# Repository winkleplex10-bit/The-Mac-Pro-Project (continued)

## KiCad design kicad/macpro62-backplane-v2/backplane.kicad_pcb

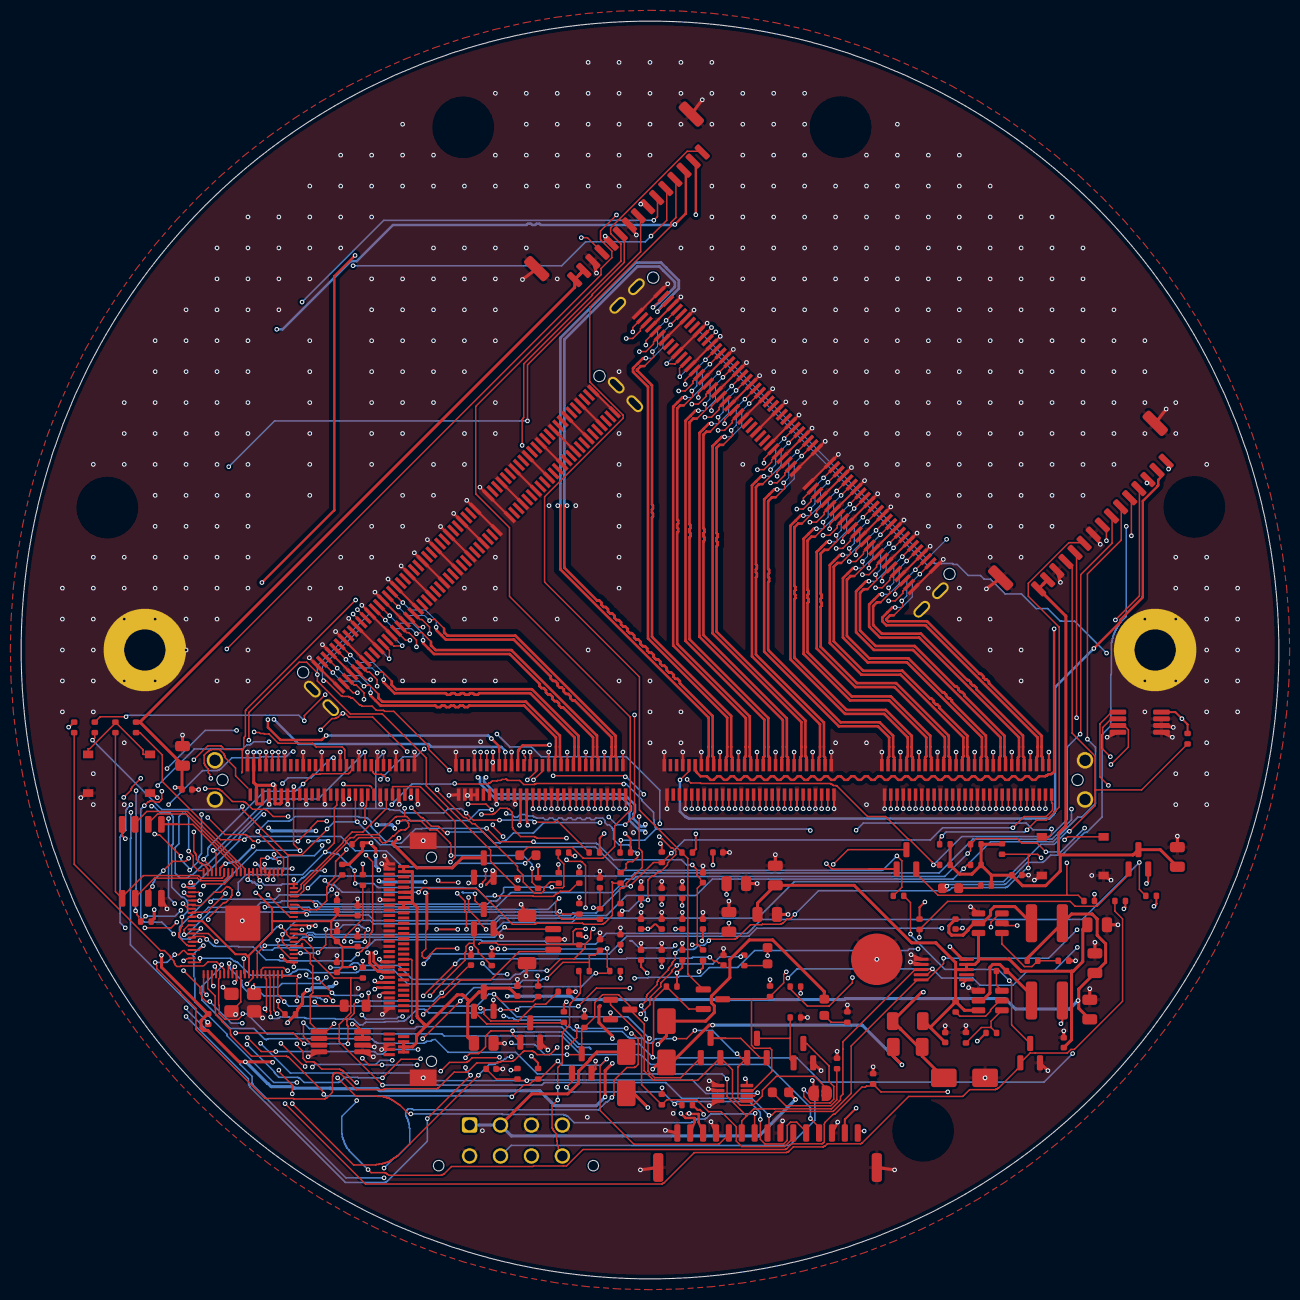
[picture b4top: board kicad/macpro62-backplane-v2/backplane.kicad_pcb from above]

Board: 4 copper layers, 122.0 x 122.0 mm, 152 parts (0 on the bottom side), 202 nets.

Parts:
C1, C5, C8, C9, C12, C14, C16, C18, C19, C21, C22, C23, C24, C25, C26, C27, C28, C32, C33, C34, C35, C38, C39: 100nF 16V X7R 0402; C_0402_1005Metric
C2, C3, C4, C6, C7, C10, C11, C13, C15, C17: 22uF 25V X5R 0805; C_0805_2012Metric
C20: 1uF 25V X5R 0402; C_0402_1005Metric
C29, C30, C31: 4.7uF 10V X5R 0402; C_0402_1005Metric
C36, C37: 15pF 50V C0G 0402; C_0402_1005Metric
D1, D2: SS34 3A 40V Schottky SMA; D_SMA
D3: SMAJ15A TVS SMA; D_SMA
D4, D5: BAT54A (LBAT54ALT1G); SOT-23
D6, D7, D8, D9, D10: LED red 0603; LED_0603_1608Metric
F1: 3A 1206 fast fuse (0466003.NRHF class); Fuse_1206_3216Metric
H1, H2: MountingHole D4 plated (GND); MountingHole_4mm_Pad
H3: M.2 2242 standoff pad (DNP option); MP62_M2_Standoff_SMT_M2_Pad5.0
J1: ME1022410103011 Mini Cool Edge 224 (C4941560, 0 s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; MP62_CPULINK_MiniCoolEdge_224P_Vertical_SMT_PLACEHOLDER
J2: Molex 43045-0812 Micro-Fit 2x4 (C277661); Molex_Micro-Fit_3.0_43045-0812_2x04_P3.00mm_Vertical
J3: BM15B-GHS-TBT (C5305069) Face P AUX; JST_GH_BM15B-GHS-TBT_1x15-1MP_P1.25mm_Vertical
J4: BM15B-GHS-TBT (C5305069) Face S AUX; JST_GH_BM15B-GHS-TBT_1x15-1MP_P1.25mm_Vertical
J6: BM15B-GHS-TBT (C5305069) IOB-LINK; JST_GH_BM15B-GHS-TBT_1x15-1MP_P1.25mm_Vertical
J7: M.2 M-key socket LOTES APCI0107 class (C841661) -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; MP62_M2_MKey_SMT_H4.2_PLACEHOLDER
J8: BM03B-SRSS-TB SWD (DNP); JST_SH_BM03B-SRSS-TB_1x03-1MP_P1.00mm_Vertical
J9: MCIO 124P RA G97R24332HR class (C4867471, 0 stock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; MP62_MCIO_124P_RA_SFF-TA-1016
J10: MCIO 124P RA (C4867471) -> Face S x4; MP62_MCIO_124P_RA_SFF-TA-1016
JP1: BENCH: bridges the Hall interlock (open = normal); SolderJumper-2_P1.3mm_Open_RoundedPad1.0x1.5mm
L1, L2: 4.7uH 2A 4x4 (SWPA4030S4R7MT); L_Changjiang_FNR4030S
L3: 3.3uH 0806 (FNR201610S3R3MT, RP2350 VREG); L_0805_2012Metric
Q1, Q2, Q3, Q5, Q6, Q7, Q8: AO3401A P-MOS; SOT-23
Q4, Q9, Q10, Q11: 2N7002 N-MOS; SOT-23
R1: 33k 1% 0402; R_0402_1005Metric
R2, R4, R7, R8, R9, R10, R13, R14, R15, R16, R17, R18, R19, R20, R21, R23, R24, R25, R26, R29, R30, R33, R34, R35, R36, R39, R40, R42, R43, R44, R45, R46, R47, R48, R49: 10k 1% 0402; R_0402_1005Metric
R3: 56k 1% 0402; R_0402_1005Metric
R5: 100k 1% 0402 (U6 EN, always on); R_0402_1005Metric
R6: 100k 1% 0402 (U7 off until the MCU enables 5V_SBY); R_0402_1005Metric
R11, R12, R55: 100k 1% 0402; R_0402_1005Metric
R22, R31, R32, R41, R54, R58, R60, R61: 1k 1% 0402; R_0402_1005Metric
R27, R28, R37, R38, R50, R51, R52, R53: 2.2k 1% 0402; R_0402_1005Metric
R56: 10k 1% 0402 (12V LED); R_0402_1005Metric
R57: 10k 1% 0402 (11V_SB LED); R_0402_1005Metric
R59, R62, R63: 33R 1% 0402; R_0402_1005Metric
R100: 10mR 1% 1W 1206 shunt; R_1206_3216Metric
SW1: BOOTSEL (TS-1187A); SW_Push_1P1T_XKB_TS-1187A
SW2: BENCH power button (TS-1187A); SW_Push_1P1T_XKB_TS-1187A
U1: RP2350B QFN-80 (C42415655); QFN-80-1EP_10x10mm_P0.4mm_EP3.4x3.4mm
U2: W25Q128JVSIQ (C97521, basic); SOIC-8_5.3x5.3mm_P1.27mm
U3: TMP1075DGKR @0x48 core side (C2864807); VSSOP-8_3x3mm_P0.65mm
U4: TMP1075DGKR @0x49 PSU side (C2864807); VSSOP-8_3x3mm_P0.65mm
U5: INA226AIDGSR @0x40 (C49851); VSSOP-10_3x3mm_P0.5mm
U6: TPS563201DDCR (C116592) -> 3V3_SB; SOT-23-6
U7: TPS563201DDCR (C116592) -> 5V_SBY; SOT-23-6
U8: SN74LVC1G74DCUR thermal latch (C70285); VSSOP-8_2.3x2mm_P0.5mm
Y1: 12MHz 3225 crystal 20pF; Crystal_SMD_3225-4Pin_3.2x2.5mm

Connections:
3V3_AUX_P: C13.1, C14.1, J3.1, J3.2, Q1.3, R26.2, R27.2, R28.2, R29.2, R30.2, R31.2
3V3_AUX_S: C15.1, C16.1, J4.1, J4.2, Q2.3, R36.2, R37.2, R38.2, R39.2, R40.2, R41.2
3V3_M2: C17.1, C18.1, J7.2, J7.4, J7.12, J7.14, J7.16, J7.18, J7.70, J7.72, J7.74, Q3.3
3V3_SB: C1.1, C6.1, C7.1, C19.1, C21.1, C22.1, C23.1, C24.1, C25.1, C26.1, C27.1, C28.1, C29.1, C38.1, D10.2, J1.B107, J1.B108, J6.1, J6.2, JP1.1, L1.2, Q1.2, Q2.2, Q3.2, Q5.2, Q6.2, R1.1, R7.2, R8.2, R9.2, R13.2, R14.2, R15.2, R16.2, R17.2, R18.2, R19.2, R20.2, R21.2, R23.2, R24.2, R25.2, R33.2, R34.2, R35.2, R42.2, R43.2, R44.2, R45.2, R46.2, R47.2, R48.2, R49.2, R50.2, R51.2, R52.2, R53.2, R59.1, U1.5, U1.15, U1.24, U1.29, U1.41, U1.50, U1.59, U1.60, U1.64, U1.68, U1.69, U1.76, U2.8, U3.8, U4.7, U4.8, U5.6, U8.8
5V_SBY: C10.1, C11.1, J1.A107, J1.A108, J1.A110, J1.A111, J1.B110, J1.B111, L2.2, R3.1
11V_SB_IN: D2.2, D9.2, J2.7
12V_MAIN_IN: D1.2, D8.2, J2.1, J2.2
AUXP_EN_N: Q1.1, R7.1, U1.37
AUXS_EN_N: Q2.1, R8.1, U1.19
BOOTSEL_N: R61.2, SW1.1
BP_OTEMP_N: D5.2, R21.1, U3.3, U4.3
BST_3V3_SB: C5.1, U6.6
BST_5V_SBY: C9.1, U7.6
CB_CARRIER_HOT_N: J1.A98, R44.1, U1.13
CB_FAN_PWM: J1.B96, U1.6
CB_FAN_TACH: J1.B98, U1.2
CB_I2C0_SCL: J1.B90, R50.1, U1.80
CB_I2C0_SDA: J1.B92, R51.1, U1.79
CB_PLTRST_N: J1.A95, R22.1, R32.1, U1.54
CB_PWRBTN_N: J1.A86, R42.1, U1.57
CB_PWR_ALERT_N: J1.A105, R43.1, U1.12
CB_RSMRST_N: J1.A92, U1.16
CB_SUS_S3_N: J1.A89, Q4.1, U1.21
CB_SUS_S45_N: J1.A90, U1.58
CB_THERMTRIP_N: D4.1, J1.A96, R18.1
CB_UART0_RX: J1.B95, U1.78
CB_UART0_TX: J1.B93, U1.77
CB_VIN_PWR_OK: J1.A93, U1.14
CC_PRSNT1_N: J1.A1, R45.1, U1.53
CC_PRSNT2_N: J1.A112, R46.1, U1.11
DVDD: C30.1, C31.1, C32.1, C33.1, C34.1, L3.2, U1.10, U1.32, U1.51, U1.65
EN_3V3: R5.1, U6.5
EN_5V: R6.1, U1.40, U7.5
FB_3V3_SB: R1.2, R2.1, U6.4
FB_5V_SBY: R3.2, R4.1, U7.4
FP_HOLD: Q10.1, R23.1, U1.36
FP_LEDA: D6.2, R31.1
FP_MCIO_PRSNT_N: J9.B12, R24.1, U1.47
FP_MOD_LED_N: D6.1, J3.15
FP_PERST_N: J9.B11, Q10.3, R22.2
FP_PRSNT_N: J3.4, R25.1, U1.42
FP_PWR_EN: J3.5, U1.49
FP_PWR_GOOD: J3.6, R26.1, U1.43
FP_REFCLK_N: J1.A52, J9.A12
FP_REFCLK_P: J1.A51, J9.A11
FP_RX0_N: J1.B49, J9.A3
FP_RX0_P: J1.B48, J9.A2
FP_RX1_N: J1.B46, J9.A6
FP_RX1_P: J1.B45, J9.A5
FP_RX2_N: J1.B43, J9.A15
FP_RX2_P: J1.B42, J9.A14
FP_RX3_N: J1.B40, J9.A18
FP_RX3_P: J1.B39, J9.A17
FP_RX4_N: J1.B37, J9.A21
FP_RX4_P: J1.B36, J9.A20
FP_RX5_N: J1.B34, J9.A24
FP_RX5_P: J1.B33, J9.A23
FP_RX6_N: J1.B31, J9.A33
FP_RX6_P: J1.B30, J9.A32
FP_RX7_N: J1.B27, J9.A36
FP_RX7_P: J1.B26, J9.A35
FP_RX8_N: J1.B24, J9.A40
FP_RX8_P: J1.B23, J9.A39
FP_RX9_N: J1.B21, J9.A43
FP_RX9_P: J1.B20, J9.A42
FP_RX10_N: J1.B18, J9.A46
FP_RX10_P: J1.B17, J9.A45
FP_RX11_N: J1.B15, J9.A49
FP_RX11_P: J1.B14, J9.A48
FP_RX12_N: J1.B12, J9.A52
FP_RX12_P: J1.B11, J9.A51
FP_RX13_N: J1.B9, J9.A55
FP_RX13_P: J1.B8, J9.A54
FP_RX14_N: J1.B6, J9.A58
FP_RX14_P: J1.B5, J9.A57
FP_RX15_N: J1.B3, J9.A61
FP_RX15_P: J1.B2, J9.A60
FP_SMB_ALERT_N: J3.10, R29.1, U1.44
FP_SMB_SCL: J3.8, R27.1, U1.56
FP_SMB_SDA: J3.9, R28.1, U1.55
FP_THERM_ALERT_N: J3.11, R30.1, U1.23
FP_THERM_TRIP_N: D4.2, J3.12, R19.1
FP_TX0_N: J1.A49, J9.B3
FP_TX0_P: J1.A48, J9.B2
FP_TX1_N: J1.A46, J9.B6
FP_TX1_P: J1.A45, J9.B5
FP_TX2_N: J1.A43, J9.B15
FP_TX2_P: J1.A42, J9.B14
FP_TX3_N: J1.A40, J9.B18
FP_TX3_P: J1.A39, J9.B17
FP_TX4_N: J1.A37, J9.B21
FP_TX4_P: J1.A36, J9.B20
FP_TX5_N: J1.A34, J9.B24
FP_TX5_P: J1.A33, J9.B23
FP_TX6_N: J1.A31, J9.B33
FP_TX6_P: J1.A30, J9.B32
FP_TX7_N: J1.A27, J9.B36
FP_TX7_P: J1.A26, J9.B35
FP_TX8_N: J1.A24, J9.B40
FP_TX8_P: J1.A23, J9.B39
FP_TX9_N: J1.A21, J9.B43
FP_TX9_P: J1.A20, J9.B42
FP_TX10_N: J1.A18, J9.B46
FP_TX10_P: J1.A17, J9.B45
FP_TX11_N: J1.A15, J9.B49
FP_TX11_P: J1.A14, J9.B48
FP_TX12_N: J1.A12, J9.B52
FP_TX12_P: J1.A11, J9.B51
FP_TX13_N: J1.A9, J9.B55
FP_TX13_P: J1.A8, J9.B54
FP_TX14_N: J1.A6, J9.B58
FP_TX14_P: J1.A5, J9.B57
FP_TX15_N: J1.A3, J9.B61
FP_TX15_P: J1.A2, J9.B60
FS_HOLD: Q11.1, R33.1, U1.17
FS_LEDA: D7.2, R41.1
FS_MCIO_PRSNT_N: J10.B12, R34.1, U1.8
FS_MOD_LED_N: D7.1, J4.15
FS_PERST_N: J10.B11, Q11.3, R32.2
FS_PRSNT_N: J4.4, R35.1, U1.9
FS_PWR_EN: J4.5, U1.1
FS_PWR_GOOD: J4.6, R36.1, U1.7
FS_REFCLK_N: J1.A71, J10.A12
FS_REFCLK_P: J1.A70, J10.A11
FS_RX0_N: J1.B68, J10.A3
FS_RX0_P: J1.B67, J10.A2
FS_RX1_N: J1.B65, J10.A6
FS_RX1_P: J1.B64, J10.A5
FS_RX2_N: J1.B62, J10.A15
FS_RX2_P: J1.B61, J10.A14
FS_RX3_N: J1.B59, J10.A18
FS_RX3_P: J1.B58, J10.A17
FS_SMB_ALERT_N: J4.10, R39.1, U1.52
FS_SMB_SCL: J4.8, R37.1, U1.4
FS_SMB_SDA: J4.9, R38.1, U1.3
FS_THERM_ALERT_N: J4.11, R40.1, U1.48
FS_THERM_TRIP_N: D5.1, J4.12, R20.1
FS_TX0_N: J1.A68, J10.B3
FS_TX0_P: J1.A67, J10.B2
FS_TX1_N: J1.A65, J10.B6
FS_TX1_P: J1.A64, J10.B5
FS_TX2_N: J1.A62, J10.B15
FS_TX2_P: J1.A61, J10.B14
FS_TX3_N: J1.A59, J10.B18
FS_TX3_P: J1.A58, J10.B17
GND: C1.2, C2.2, C3.2, C4.2, C6.2, C7.2, C8.2, C10.2, C11.2, C12.2, C13.2, C14.2, C15.2, C16.2, C17.2, C18.2, C19.2, C20.2, C21.2, C22.2, C23.2, C24.2, C25.2, C26.2, C27.2, C28.2, C29.2, C30.2, C31.2, C32.2, C33.2, C34.2, C35.2, C36.2, C37.2, C38.2, C39.2, D3.2, H1.1, H2.1, H3.1, J1.A4, J1.A7, J1.A10, J1.A13, J1.A16, J1.A19, J1.A22, J1.A25, J1.A28, J1.A29, J1.A32, J1.A35, J1.A38, J1.A41, J1.A44, J1.A47, J1.A50, J1.A53, J1.A56, J1.A57, J1.A60, J1.A63, J1.A66, J1.A69, J1.A72, J1.A75, J1.A78, J1.A81, J1.A82, J1.A83, J1.A84, J1.A85, J1.A88, J1.A91, J1.A94, J1.A97, J1.A100, J1.A103, J1.A106, J1.A109, J1.B1, J1.B4, J1.B7, J1.B10, J1.B13, J1.B16, J1.B19, J1.B22, J1.B25, J1.B28, J1.B29, J1.B32, J1.B35, J1.B38, J1.B41, J1.B44, J1.B47, J1.B50, J1.B53, J1.B56, J1.B57, J1.B60, J1.B63, J1.B66, J1.B69, J1.B72, J1.B75, J1.B78, J1.B81, J1.B84, J1.B85, J1.B88, J1.B91, J1.B94, J1.B97, J1.B100, J1.B103, J1.B106, J1.B109, J1.B112, J1.BL, J2.3, J2.4, J2.5, J3.3, J3.7, J3.MP, J4.3, J4.7, J4.MP, J6.3, J6.7, J6.12, J6.15, J6.MP, J7.1, J7.3, J7.9, J7.15, J7.21, J7.27, J7.33, J7.39, J7.45, J7.51, J7.57, J7.71, J7.73, J7.MP, J8.2, J8.MP, J9.A1, J9.A4, J9.A7, J9.A10, J9.A13, J9.A16, J9.A19, J9.A22, J9.A25, J9.A28, J9.A31, J9.A34, J9.A37, J9.A38, J9.A41, J9.A44, J9.A47, J9.A50, J9.A53, J9.A56, J9.A59, J9.A62, J9.B1, J9.B4, J9.B7, J9.B10, J9.B13, J9.B16, J9.B19, J9.B22, J9.B25, J9.B28, J9.B31, J9.B34, J9.B37, J9.B38, J9.B41, J9.B44, J9.B47, J9.B50, J9.B53, J9.B56, J9.B59, J9.B62, J9.MP, J10.A1, J10.A4, J10.A7, J10.A10, J10.A13, J10.A16, J10.A19, J10.A22, J10.A25, J10.A28, J10.A31, J10.A34, J10.A37, J10.A38, J10.A41, J10.A44, J10.A47, J10.A50, J10.A53, J10.A56, J10.A59, J10.A62, J10.B1, J10.B4, J10.B7, J10.B10, J10.B13, J10.B16, J10.B19, J10.B22, J10.B25, J10.B28, J10.B31, J10.B34, J10.B37, J10.B38, J10.B41, J10.B44, J10.B47, J10.B50, J10.B53, J10.B56, J10.B59, J10.B62, J10.MP, Q4.2, Q9.2, Q10.2, Q11.2, R2.2, R4.2, R6.2, R10.2, R11.2, R12.2, R55.2, R56.2, R57.2, SW1.2, SW2.2, U1.62, U1.81, U2.4, U3.4, U3.5, U3.6, U3.7, U4.4, U4.5, U4.6, U5.1, U5.2, U5.7, U6.1, U7.1, U8.1, U8.2, U8.4, Y1.2, Y1.4
HALL_A_N: J6.5, Q5.1, R13.1
HALL_B_N: J6.6, Q6.1, R14.1
I2C_SYS_SCL: J6.8, R52.1, U1.46, U3.2, U4.2, U5.5
I2C_SYS_SDA: J6.9, R53.1, U1.45, U3.1, U4.1, U5.4
ILK_A: JP1.2, Q5.3, Q6.3, Q7.2, R11.1, U1.38
ILK_B: Q7.3, Q8.2
IOB_PRSNT_N: J6.11, R48.1, U1.22
LATCH_CLR_N: C20.1, R16.1, U1.28, U8.6
LED11_K: D9.1, R57.1
LED12_K: D8.1, R56.1
LED_ST_K: D10.1, R58.1
M2_DEVSLP: J7.38, R10.1
M2_EN_N: Q3.1, Q4.3, R9.1
MCU_LED_N: R58.2, U1.18
MCU_RUN: C39.1, U1.35
MCU_SWCLK: J8.1, U1.33
MCU_SWDIO: J8.3, U1.34
PSON_DRV: Q8.3, Q9.1, R12.1
PSU_PS_ON_N: J2.6, Q9.3
PSU_PWR_OK: J2.8, R54.1
PSU_PWR_OK_M: R54.2, R55.1, U1.20
PS_ON_REQ_N: Q7.1, R15.1, U1.39
PWRBTN_IN_N: J6.4, R49.1, SW2.1, U1.25
QSPI_SCLK: U1.71, U2.6
QSPI_SD0: U1.72, U2.5
QSPI_SD1: U1.74, U2.2
QSPI_SD2: U1.73, U2.3
QSPI_SD3: U1.70, U2.7
QSPI_SS: R61.1, U1.75, U2.1
SATA0_RX_N: J1.B71, J7.43
SATA0_RX_P: J1.B70, J7.41
SATA0_TX_N: J1.A74, J7.47
SATA0_TX_P: J1.A73, J7.49
SW_3V3_SB: C5.2, L1.1, U6.2
SW_5V_SBY: C9.2, L2.1, U7.2
SYS_INT_N: J6.10, R47.1, U1.26, U5.3
THERM_LATCH: Q8.1, U1.27, U8.5
TRIP_N: D4.3, D5.3, R17.1, U8.7
USB2_FACEP_N: J1.B52, J3.14
USB2_FACEP_P: J1.B51, J3.13
USB2_FACES_N: J1.B77, J4.14
USB2_FACES_P: J1.B76, J4.13
USB2_MCU_N: J1.B74, R63.2
USB2_MCU_P: J1.B73, R62.2
USB2_SPARE_N: J1.B80, J6.14
USB2_SPARE_P: J1.B79, J6.13
USB_DM_M: R63.1, U1.66
USB_DP_M: R62.1, U1.67
VIN: C2.1, C3.1, C4.1, C8.1, C12.1, R5.2, R100.2, U5.8, U5.9, U6.3, U7.3
VIN_F: D3.1, F1.2, R100.1, U5.10
VIN_OR: D1.1, D2.1, F1.1
VREG_AVDD: C35.1, R59.2, U1.61
VREG_LX: L3.1, U1.63
XIN: C36.1, U1.30, Y1.1
XOUT: R60.1, U1.31
XOUT_C: C37.1, R60.2, Y1.3
